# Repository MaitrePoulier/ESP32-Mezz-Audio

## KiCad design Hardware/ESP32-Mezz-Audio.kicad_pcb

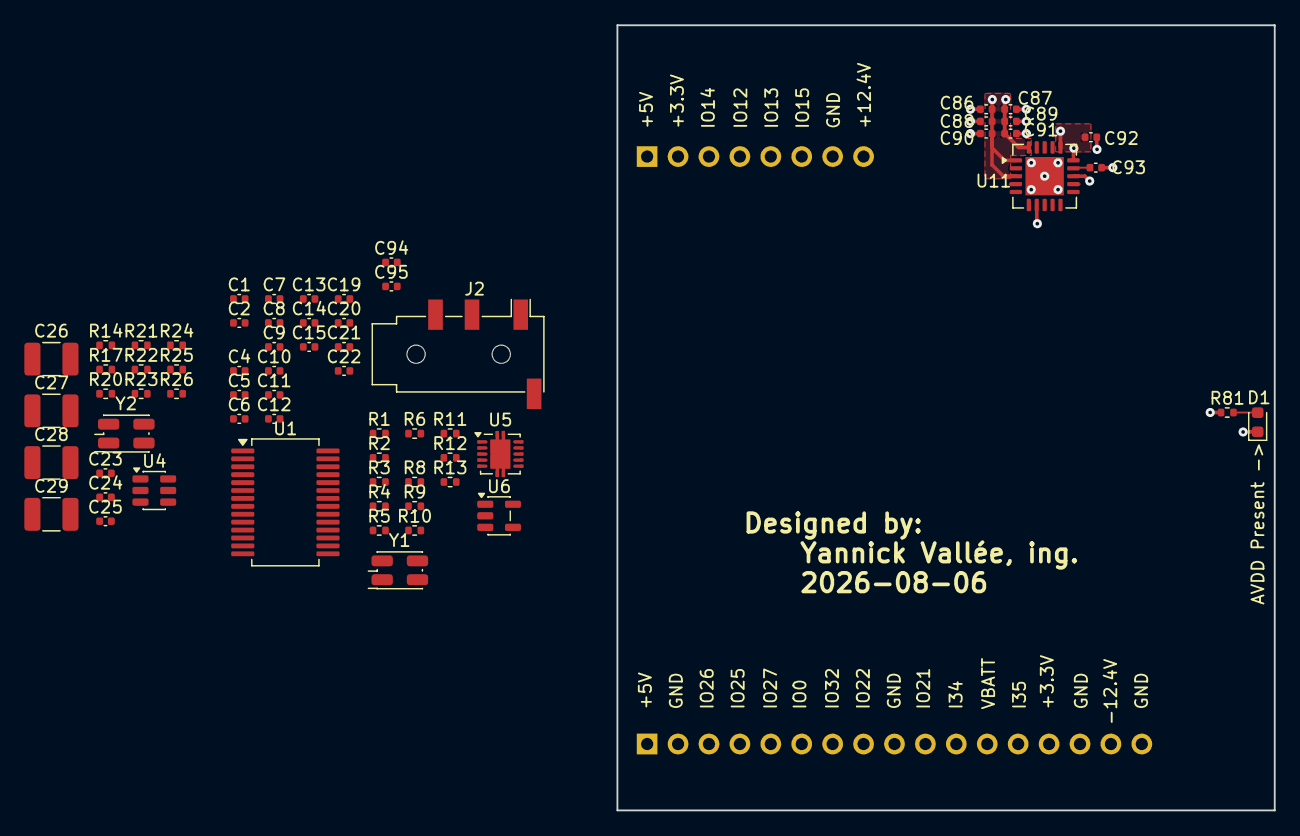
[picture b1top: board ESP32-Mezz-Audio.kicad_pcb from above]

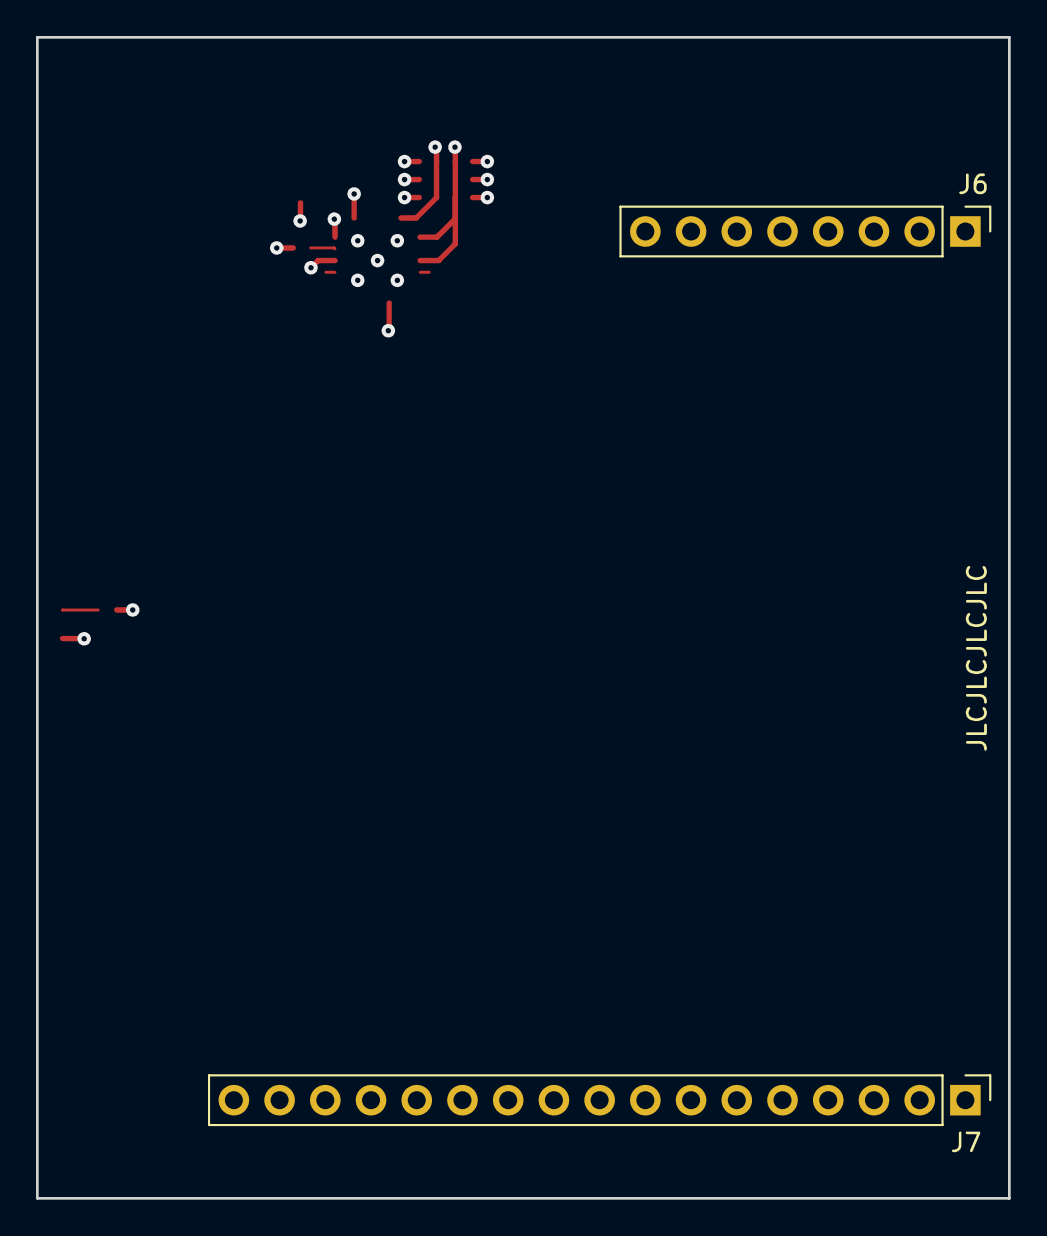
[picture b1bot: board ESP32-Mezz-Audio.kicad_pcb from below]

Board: 4 copper layers, 54.0 x 64.5 mm, 68 parts (2 on the bottom side), 39 nets.

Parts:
C1, C6, C8, C9: 100pF; C_0402_1005Metric
C2, C5, C11, C12, C14, C15, C19, C20, C21, C22, C23, C24, C25: 220nF; C_0402_1005Metric
C4, C7, C10, C13: 560pF; C_0402_1005Metric
C26, C27, C28, C29: 47uF; C_1210_3225Metric_Pad1.33x2.70mm_HandSolder
C86, C87, C88, C89, C91, C92, C94, C95: 10uF; C_0402_1005Metric
C90: 4.7nF; C_0402_1005Metric
C93: 1uF; C_0402_1005Metric
D1: Green, 3.2V; LED_0603_1608Metric
J2: Conn-AudioJack; Jack_3.5mm_PJ320D_Horizontal
J6: HC-PZ254-11.5L-1x8PZ; PinHeader_1x08_P2.54mm_Vertical
J7: HC-PZ254-11.5L-1x17PZ; PinHeader_1x17_P2.54mm_Vertical
R1, R4, R8, R9: 2.32k; R_0402_1005Metric
R2, R5, R10, R11: 1.58k; R_0402_1005Metric
R3, R6, R12, R13: 560R; R_0402_1005Metric
R14, R17, R20: 33Ω; R_0402_1005Metric
R21, R22, R23, R24, R25, R26: 10k; R_0402_1005Metric
R81: 1.18k; R_0402_1005Metric
U1: PCM1794A; SSOP-28_5.3x10.2mm_P0.65mm
U4: SN74LVC2G34; SOT-23-6
U5: OPA1622; Texas_S-PVSON-N10
U6: TPS7A2033; SOT-23-5
U11: TPS7A4700; Texas_RGW0020A_VQFN-20-1EP_5x5mm_P0.65mm_EP3.15x3.15mm
Y1: SX3M24.576B20F30TNF; Oscillator_SMD_EuroQuartz_XO32-4Pin_3.2x2.5mm_RotB_HandSold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
Y2: SX3M22.5792B20F30TNF; Oscillator_SMD_EuroQuartz_XO32-4Pin_3.2x2.5mm_RotB_HandSold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

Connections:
+3.3V: C22.2, J6.2, J7.14, R22.1, R23.1, U1.9 (VDD)
+5.5V: C92.1, C94.1, J7.1, U6.1 (IN), U6.3 (EN), U11.13 (EN), U11.15 (IN), U11.16 (IN)
+12.4V: C2.1, C11.1, C14.1, C29.1, J6.8, R25.1, U5.2 (V+)
-12.4V: C5.1, C12.1, C15.1, C28.1, J7.16, U5.4 (V-), U5.11 (V-)
/ESP32-Mezz-Audio/EN: R25.2, U5.8 (EN)
/ESP32-Mezz-Audio/LeftAudio: C7.2, J2.T, R6.2, U5.9
/ESP32-Mezz-Audio/Right Audio: C13.2, J2.R1, R13.2, U5.7
/ESP32-Mezz-Audio/SCK: R14.2, R17.2, U1.7 (SCK), U4.1 (INA1)
AVDD: C19.2, C20.2, C21.2, C26.1, C27.1, C86.1, C87.1, C88.1, C89.1, C90.1, C91.1, R81.1, U1.15 (VCC2R), U1.23 (VCC1), U1.28 (VCC2L), U11.1 (OUT), U11.3 (SENSE/FB), U11.20 (OUT)
CLK_22p5792en: J7.8, R24.1, Y2.1 (EN)
CLK_24p5760en: J7.7, R23.2, Y1.1 (EN)
Clk-3V3: C23.2, C24.2, C25.2, C95.1, U4.5 (VCC), U6.5 (OUT), Y1.4 (V+), Y2.4 (V+)
GND: C2.2, C4.2, C5.2, C10.2, C11.2, C12.2, C14.2, C15.2, C19.1, C20.1, C21.1, C22.1, C23.1, C24.1, C25.1, C28.2, C29.2, C86.2, C87.2, C88.2, C89.2, C90.2, C91.2, C92.2, C93.2, C94.2, C95.2, D1.1 (K), J2.R2, J6.7, J7.2, J7.9, J7.15, J7.17, R3.2, R12.2, R21.2, R24.2, R26.2, U1.1 (MONO), U1.2 (CHSL), U1.3 (DEM), U1.8 (DGND), U1.11 (FMT0), U1.12 (FMT1), U1.16 (AGND3R), U1.19 (AGND1), U1.24 (AGND2), U1.27 (AGND3L), U4.2 (GND), U4.3 (INA2), U5.3 (GND), U6.2 (GND), U11.6 (3.2V), U11.7 (GND), U11.10 (0.4V), U11.21 (PAD), Y1.2 (GND), Y2.2 (GND)
I2S_BCK: J7.5, U1.6 (BCK)
I2S_DATA: J7.4, U1.5 (DATA)
I2S_LRCK: J7.3, U1.4 (LRCK)
MUTE: J7.10, R22.2, U1.10 (MUTE)
unnamed: C1.2, R1.2, R2.1
unnamed: C6.2, R4.2, R5.1
unnamed: C8.2, R8.2, R10.1
unnamed: C9.2, R9.2, R11.1
unnamed: D1.2 (A), R81.2
unnamed: C1.1, R1.1, U1.25 (IOUTL+)
unnamed: C6.1, R4.1, U1.26 (IOUTL-)
unnamed: C8.1, R8.1, U1.17 (IOUTR+)
unnamed: C9.1, R9.1, U1.18 (IOUTR-)
unnamed: R26.1, U1.20 (IREF)
unnamed: C26.2, U1.22 (VCOML)
unnamed: C27.2, U1.21 (VCOMR)
unnamed: R20.1, U4.6 (Y1)
unnamed: C4.1, R3.1, R5.2, U5.1 (+)
unnamed: C7.1, R2.2, R6.1, U5.10 (-)
unnamed: C10.1, R11.2, R12.1, U5.5 (+)
unnamed: C13.1, R10.2, R13.1, U5.6 (-)
unnamed: C93.1, U11.14 (NR)
unnamed: R14.1, Y1.3 (OUT)
unnamed: R17.1, Y2.3 (OUT)
REFCLK: J7.6, R20.2
RSTn: J7.11, R21.1, U1.14 (~RST)

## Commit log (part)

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2026-06-24 Copy of BaseBoard
2026-06-24 Adding ADC and opamps
